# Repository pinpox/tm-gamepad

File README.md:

# tm-gamepad

Custom gamepad for Trackmania using a Waveshare RP2040-Zero and Lekker analog
switches

## BOM

- 1x [Waveshare RP2040-Zero](https://www.waveshare.com/wiki/RP2040-Zero)
- 4x 49E Hall-Effect Sensor
- 4x [Lekker switches](https://wooting.io/product/lekker-switch-linear60)

## References

- https://content.instructables.com/ORIG/FHV/BQO4/JVR5YV9R/FHVBQO4JVR5YV9R.pdf

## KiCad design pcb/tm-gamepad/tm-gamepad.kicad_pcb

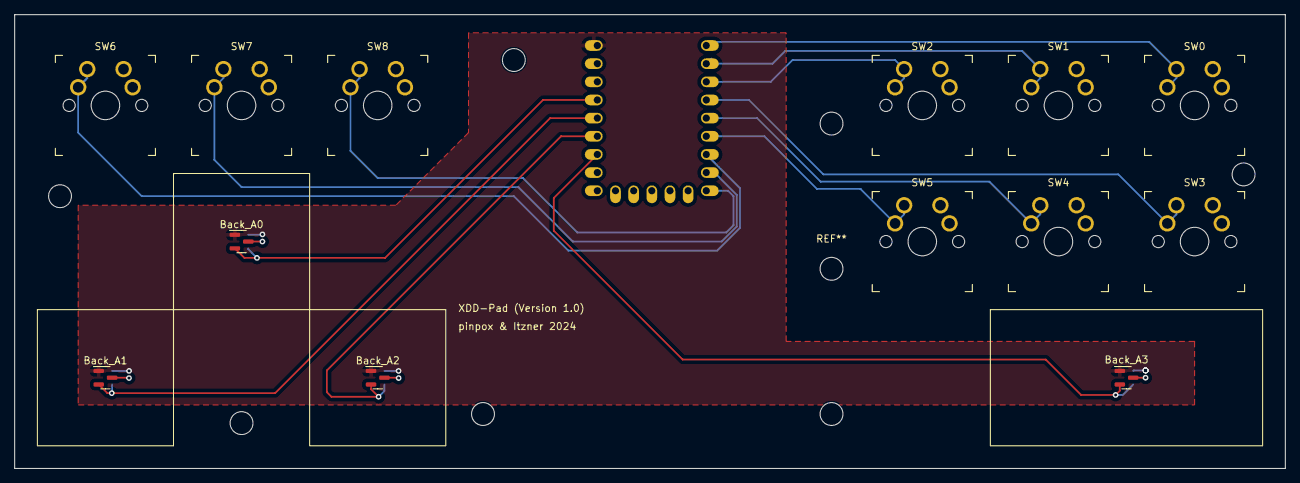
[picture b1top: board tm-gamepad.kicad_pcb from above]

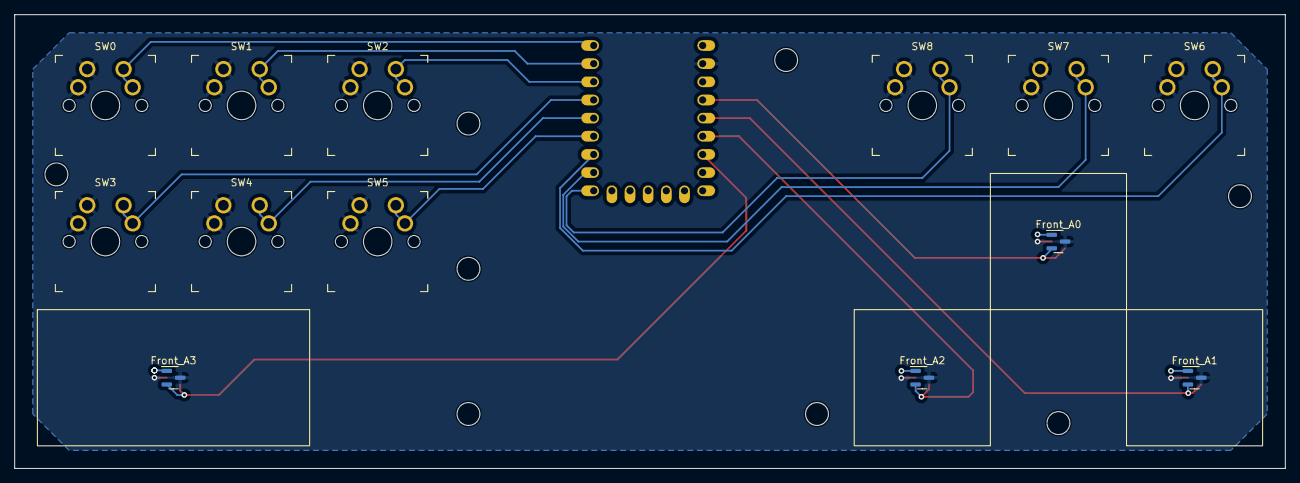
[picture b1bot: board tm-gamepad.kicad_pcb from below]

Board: 2 copper layers, 177.8 x 63.5 mm, 18 parts (4 on the bottom side), 15 nets.

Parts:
Back_A0, Back_A1, Back_A2: SOT-23_Cherry_MX1u
Back_A3: SOT-23_Cherry_MX2u
Front_A0, Front_A1, Front_A2: SOT-23_Cherry_MX1u
Front_A3: SOT-23_Cherry_MX2u
SW0, SW1, SW2, SW3, SW4, SW5, SW6, SW7, SW8: SW_Push_Dual; SW_MX_reversible
U5: rp2040-zero; rp2040-zero-tht

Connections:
5V: Back_A0.1 (VCC), Back_A1.1 (VCC), Back_A2.1 (VCC), Back_A3.1 (VCC), Front_A0.1 (VCC), Front_A1.1 (VCC), Front_A2.1 (VCC), Front_A3.1 (VCC), U5.23 (5V)
Digital0: SW0.1, U5.1 (0)
Digital1: SW1.1, U5.2 (1)
Digital2: SW2.1, U5.3 (2)
Digital3: SW3.1, U5.4 (3)
Digital4: SW4.1, U5.5 (4)
Digital5: SW5.1, U5.6 (5)
Digital6: SW6.1, U5.7 (6)
Digital7: SW7.1, U5.8 (7)
Digital8: SW8.1, U5.9 (8)
GND: Back_A0.3 (GND), Back_A1.3 (GND), Back_A2.3 (GND), Back_A3.3 (GND), Front_A0.3 (GND), Front_A1.3 (GND), Front_A2.3 (GND), Front_A3.3 (GND), SW0.2, SW1.2, SW2.2, SW3.2, SW4.2, SW5.2, SW6.2, SW7.2, SW8.2, U5.22 (GND)
unnamed: Back_A0.2 (OUT), Front_A0.2 (OUT), U5.20 (29)
unnamed: Back_A1.2 (OUT), Front_A1.2 (OUT), U5.19 (28)
unnamed: Back_A2.2 (OUT), Front_A2.2 (OUT), U5.18 (27)
unnamed: Back_A3.2 (OUT), Front_A3.2 (OUT), U5.17 (26)

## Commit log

2024-01-29 Add 4 hall sensors
2024-01-29 Add folders
2024-01-30 Add kicad files
2024-02-16 Add script to plot values
